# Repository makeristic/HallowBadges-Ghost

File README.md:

# HallowBadges-Ghost

Ghost-shaped Halloween PCB badge with two flashing LEDs, an ATtiny13A microcontroller and CR2032 coin-cell power. Designed by Michael Cutler in 2020, with KiCad source, fabrication files and an Arduino example.

**Status:** Boards were manufactured by [JLCPCB](https://jlcpcb.com/). The firmware example now compiles with the toolchain below. The hardware audit found remaining fabrication and assembly issues: review the [audit report](docs/code-audit-report.md) before a new manufacturing run.

* The original project reported about 6 days / 144 hours from one CR2032 battery; runtime depends on the LEDs, firmware and battery.
* The board also features an optional surface-mount 2.54mm connector which is [Simple Add-ons (SAO)](https://hackaday.io/project/175182-simple-add-ons-sao) compatible so you can power the badges externally.
* You can program the device using a [SOIC-8 Test Clip](https://www.digikey.com/en/products/detail/mueller-electric-co/BU-P5250/9675948) or similar, I attached it to an Arduino-as-ISP setup.

Render of the Front:

Render of the Back:

The finished product:

## Video

I've uploaded a quick video of the boards in action here:

## Hardware

The two-layer PCB uses an ATtiny13A-SSU in SOIC-8, two 0805 LEDs, a BSS138 MOSFET and 0805 resistors. The optional SAO connector is a surface-mount 2×3 header on 2.54 mm pitch.

### Files and fabrication

* [Schematic PDF](HallowBadges-schematic.pdf) — view the circuit without installing KiCad.
* [Bill of materials](HallowBadges-BOM.csv) — references, footprints and datasheet links.
* [KiCad project](HallowBadges.pro), [schematic](HallowBadges.sch) and [PCB layout](HallowBadges.kicad_pcb) — editable source.
* [Legacy schematic symbol cache](HallowBadges-cache.lib) — complete KiCad 5.1.7 symbol definitions for loading the schematic independently of global symbol libraries.
* [Gerber and drill files](gerber/) — original manufacturing exports, including a Gerber job file.
* [Custom outline footprint](HallowBadges.pretty/) — the ghost artwork and board outline.
* [Images](images/) and [component references](datasheets/) — photographs, renders and reference material.
* [Arduino sketch](firmware/HallowBadges/HallowBadges.ino) — the flashing-LED example.

The board and Gerber job headers identify **KiCad 5.1.7**. Open `HallowBadges.pro` and keep `HallowBadges-cache.lib` beside the schematic. The restored cache supplies all seven symbol definitions from the pinned KiCad 5.1.7 libraries; [provenance and upstream terms](THIRD_PARTY.md) are included. The project [footprint library table](fp-lib-table) registers `HallowBadges.pretty` as `HallowBadges`; keep that directory beside the project. Standard KiCad footprint and 3D libraries are still needed for library updates and complete renders. If using a newer KiCad release, migrate a copy and inspect the converted schematic, footprints and design rules before regenerating outputs.

The files in `gerber/` are the historical 2020 manufacturing exports. The editable PCB and custom footprint have since had two zero-length outline segments removed; their nonzero contour, copper and connectivity are unchanged. Review the remaining DRC findings in the [audit report](docs/code-audit-report.md), then regenerate and inspect manufacturing outputs before a new run. The historical exports have not been replaced by unchecked nightly-KiCad output.

For assembly, check component polarity and confirm component values before ordering. The existing BOM uses generic `R_Small` resistor values and `LED_Small` LED entries, so it is not a complete procurement list.

H1 and H2 appear in the schematic and BOM but have no footprints on this PCB. The coin-cell and SAO supply share VCC directly, with no source isolation: remove the coin cell before applying external power or powering the board from an ISP programmer. J1 is an SAO connector, not a six-pin ISP connector.

I created three designs, each can be found on Github:

* [HallowBadges-Bat](https://github.com/makeristic/HallowBadges-Bat)
* [HallowBadges-Ghost](https://github.com/makeristic/HallowBadges-Ghost)
* [HallowBadges-Pumpkin](https://github.com/makeristic/HallowBadges-Pumpkin)

## Software

The [downloadable Arduino sketch](firmware/HallowBadges/HallowBadges.ino) blinks both LEDs together through Q1. It uses the `randomSeed` and `random` APIs supported by [MicroCore 2.5.2](https://github.com/MCUdude/MicroCore/tree/v2.5.2). The original `tiny_srandom` and `tiny_random` names were not defined by that core.

`GPIO1` is PB0 / OC0A (physical SOIC pin 5), so `PIN_PB0` selects the hardware PWM output driving Q1 through R3. `A3` is the unused PB3 input (physical pin 2). The mapping follows the [MicroCore pin definitions](https://github.com/MCUdude/MicroCore/blob/v2.5.2/avr/variants/attiny13a/pins_arduino.h) and the [ATtiny13A datasheet](https://ww1.microchip.com/downloads/en/DeviceDoc/ATtiny13A-Data-Sheet-DS40002307A.pdf).

Compile from the repository root with Arduino CLI:

```sh
arduino-cli core update-index --additional-urls https://mcudude.github.io/MicroCore/package_MCUdude_MicroCore_index.json
arduino-cli core install MicroCore:avr@2.5.2 --additional-urls https://mcudude.github.io/MicroCore/package_MCUdude_MicroCore_index.json
arduino-cli compile --fqbn MicroCore:avr:13:clock=1M2,BOD=disabled,eeprom=keep,bootloader=no_bootloader --warnings all firmware/HallowBadges
```

This configuration was compile-checked with Arduino CLI 1.5.1 and AVR GCC 7.3.0. It is a 1.2 MHz, no-bootloader build configuration; compiling does not program fuses. The original boards' clock and fuse settings were not recorded, so confirm that the actual clock matches the selected build before programming.

The original boards were programmed with Arduino-as-ISP and a SOIC-8 clip. ISP requires RESET (pin 1), MOSI (pin 5), MISO (pin 6), SCK (pin 7), VCC (pin 8) and GND (pin 4). Verify clip orientation and power before connection. The updated sketch has not been uploaded to a physical badge.

## Licence

This work retains its existing [Creative Commons Attribution-ShareAlike 4.0 International licence](https://creativecommons.org/licenses/by-sa/4.0/). The full text is in [LICENSE](LICENSE). Attribute Michael Cutler / Makeristic and preserve the licence when sharing adaptations.

Third-party component datasheets, pinout reference images and KiCad library material retain their respective owners' rights and notices; the project licence does not relicense those materials. The restored symbol cache is covered by the upstream [KiCad library licence and electronic-design exception](LICENSE-KiCad.md), with attribution and source details in [THIRD_PARTY.md](THIRD_PARTY.md).

## Questions and contributions

Use [GitHub Issues](https://github.com/makeristic/HallowBadges-Ghost/issues) for questions, build reports or design problems. Include the repository revision, KiCad version and relevant photos or measurements. Pull requests should explain the change and keep editable source and regenerated manufacturing outputs consistent. For a documentation-only change, leave manufacturing files unchanged.

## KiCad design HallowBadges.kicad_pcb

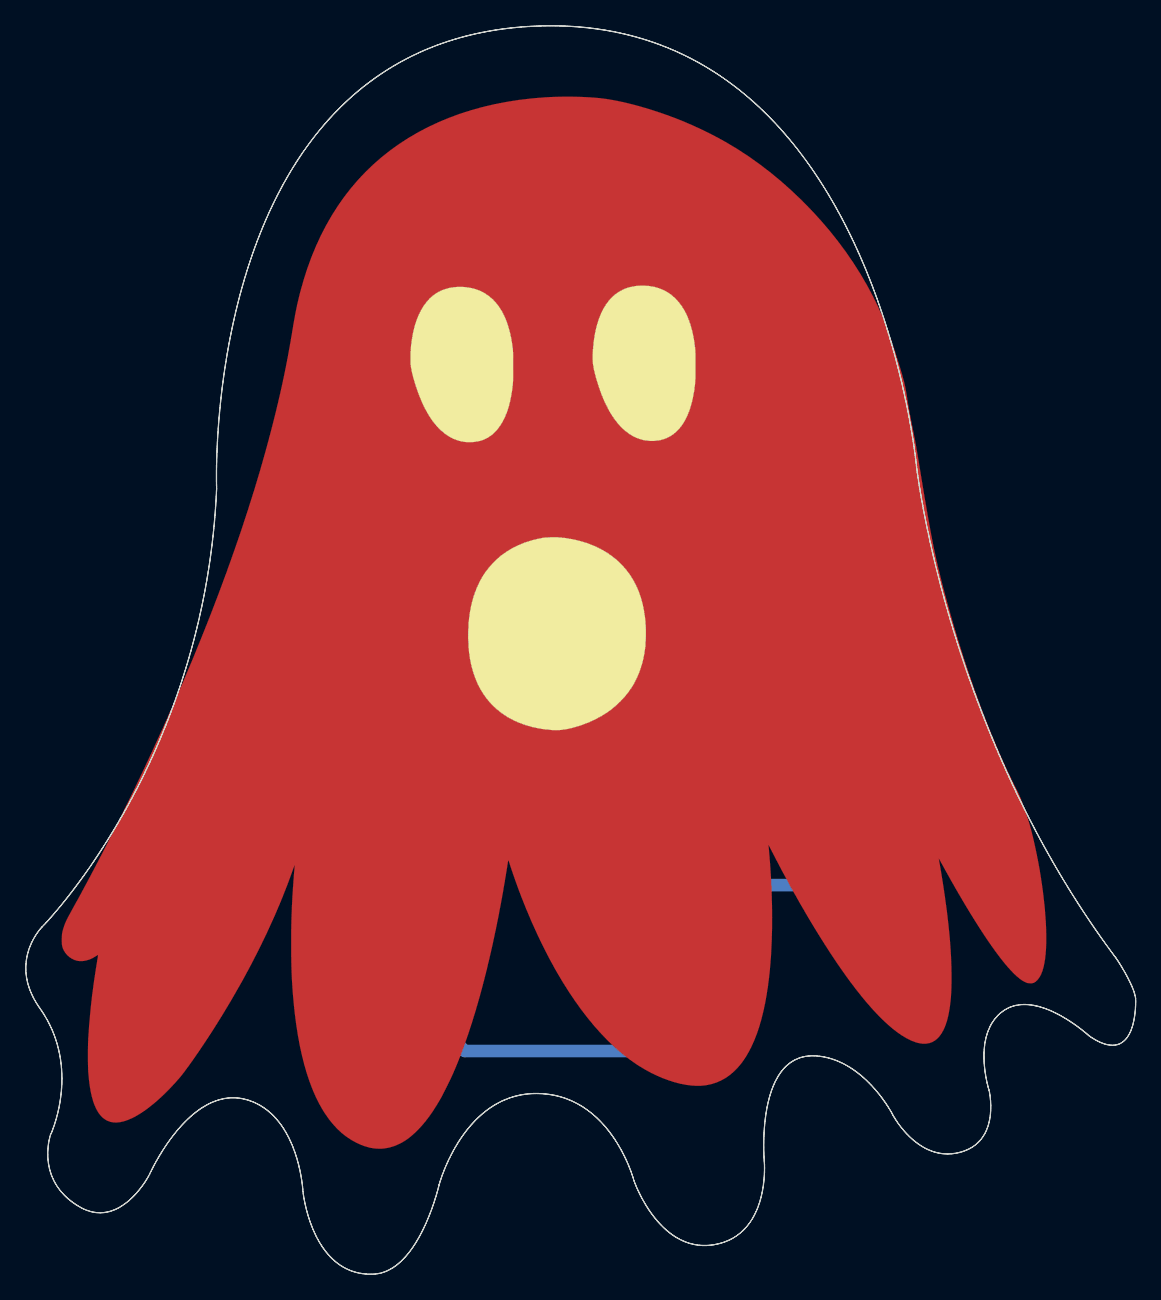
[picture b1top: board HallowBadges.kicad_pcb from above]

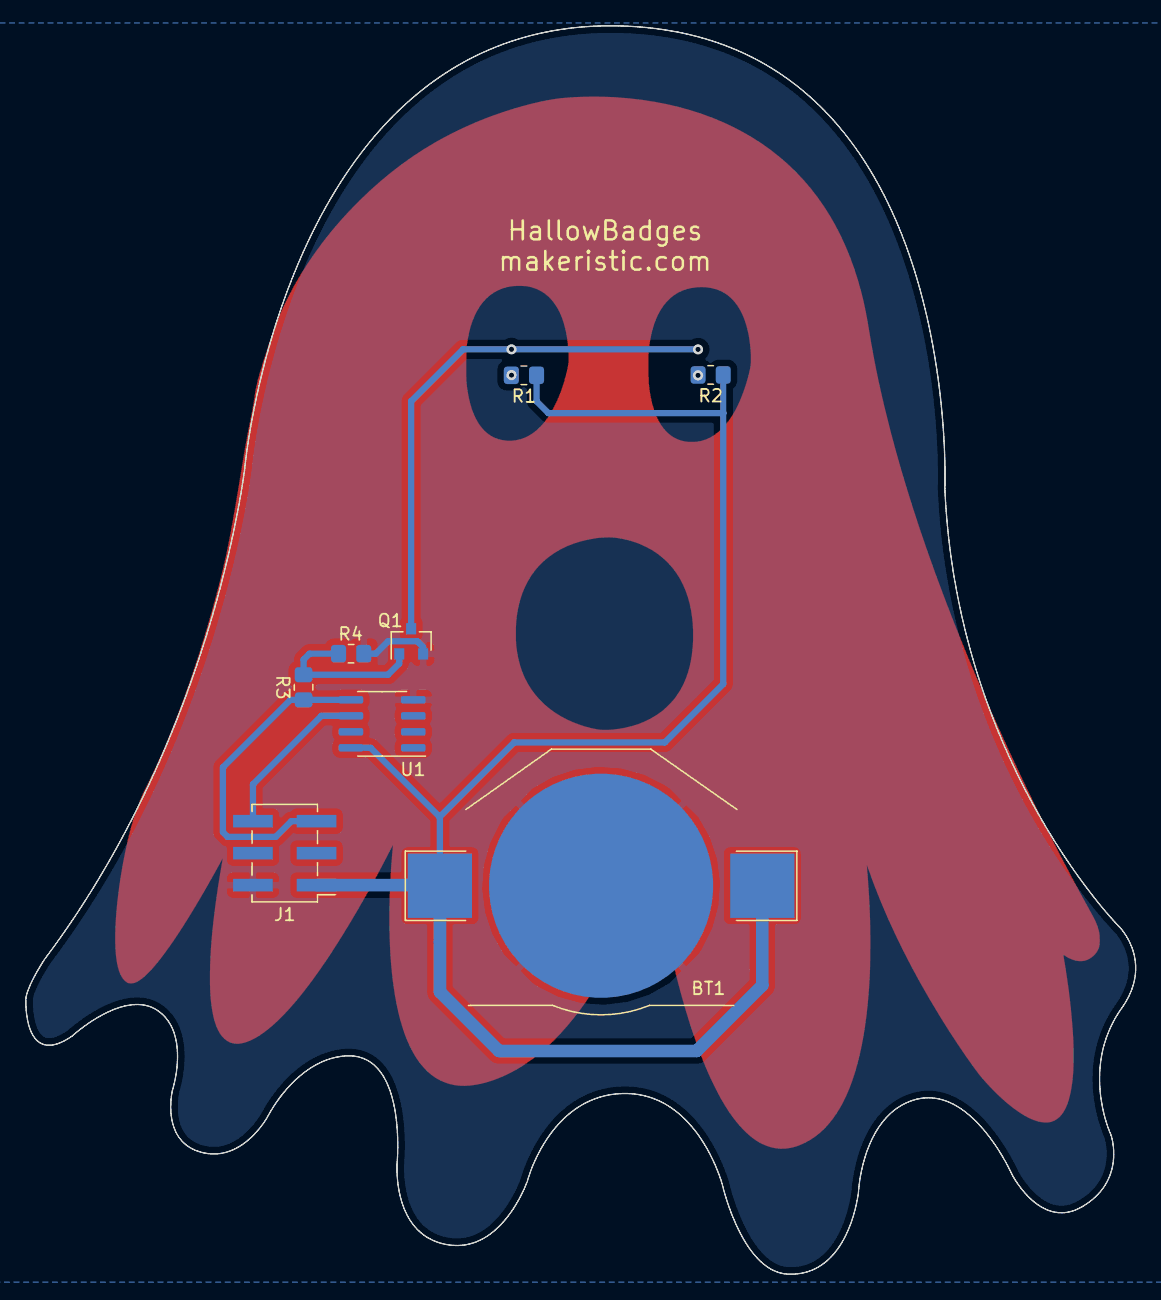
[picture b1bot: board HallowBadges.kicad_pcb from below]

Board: 2 copper layers, 88.1 x 99.1 mm, 11 parts (8 on the bottom side), 8 nets.

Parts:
BT1: Battery_Cell; BatteryHolder_Keystone_3002_1x2032
D1, D2: LED_Small; LED_0805_2012Metric_Pad1.15x1.40mm_HandSolder
J1: Conn_02x03_Simple_Add_On; PinHeader_2x03_P2.54mm_Vertical_SMD
Q1: BSS138; SOT-23
R1, R2, R3, R4: R_Small; R_0805_2012Metric_Pad1.20x1.40mm_HandSolder
Ref**: Val**; ghost-outline
U1: ATtiny13A-SSU; SOIC-8_3.9x4.9mm_P1.27mm

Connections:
GND: BT1.2, J1.2, Q1.2, R4.1, U1.4
GPIO1: J1.5, R3.2, U1.5
GPIO2: J1.6, U1.6
unnamed: D1.1, D2.1, Q1.3
unnamed: D1.2, R1.2
unnamed: D2.2, R2.2
unnamed: Q1.1, R3.1, R4.2
VCC: BT1.1, J1.1, R1.1, R2.1, U1.8

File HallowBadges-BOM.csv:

Reference, Value, Footprint, Datasheet
"R4","R_Small","Resistor_SMD:R_0805_2012Metric_Pad1.20x1.40mm_HandSolder","~"
"H2","MountingHole_Pad","MountingHole:MountingHole_2.7mm_M2.5_Pad","~"
"H1","MountingHole_Pad","MountingHole:MountingHole_2.7mm_M2.5_Pad","~"
"R3","R_Small","Resistor_SMD:R_0805_2012Metric_Pad1.20x1.40mm_HandSolder","~"
"Q1","BSS138","Package_TO_SOT_SMD:SOT-23","https://www.onsemi.com/pub/Collateral/BSS138-D.PDF"
"R2","R_Small","Resistor_SMD:R_0805_2012Metric_Pad1.20x1.40mm_HandSolder","~"
"R1","R_Small","Resistor_SMD:R_0805_2012Metric_Pad1.20x1.40mm_HandSolder","~"
"D2","LED_Small","LED_SMD:LED_0805_2012Metric_Pad1.15x1.40mm_HandSolder","~"
"D1","LED_Small","LED_SMD:LED_0805_2012Metric_Pad1.15x1.40mm_HandSolder","~"
"U1","ATtiny13A-SSU","Package_SO:SOIC-8_3.9x4.9mm_P1.27mm","http://ww1.microchip.com/downloads/en/DeviceDoc/doc8126.pdf"
"BT1","Battery_Cell","Battery:BatteryHolder_Keystone_3002_1x2032","https://www.memoryprotectiondevices.com/datasheets/BC-2003-d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"
"J1","Conn_02x03_Simple_Add_On","Connector_PinHeader_2.54mm:PinHeader_2x03_P2.54mm_Vertical_SMD","https://hackaday.io/project/175182-simple-add-ons-sao"

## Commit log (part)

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2020-11-16 Added images
2020-11-16 More images
2020-11-16 Updated image
